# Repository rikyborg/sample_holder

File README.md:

# sample_holder
KTH Nanophys Sample holder

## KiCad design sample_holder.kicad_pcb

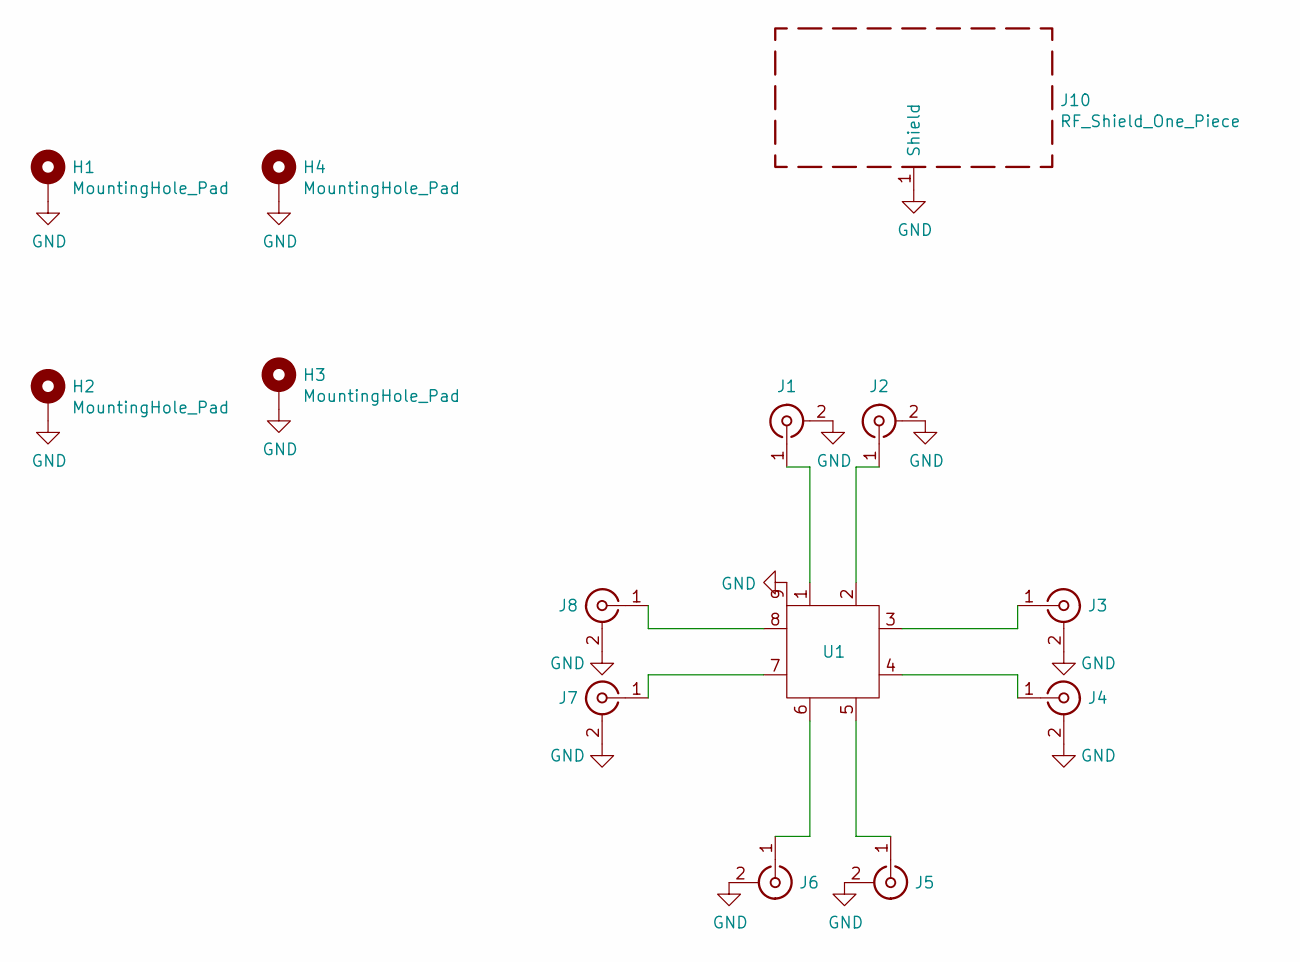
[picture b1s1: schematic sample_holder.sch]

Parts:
H1, H2, H3, H4: MountingHole_Pad; MountingHole_3.5mm_Pad
J1, J2, J3, J4, J5, J6, J7, J8: Conn_Coaxial; 0732513481
J10: RF_Shield_One_Piece; cage
U1: sample

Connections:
GND: H1.1, H2.1, H3.1, H4.1, J1.2 (Ext), J2.2 (Ext), J3.2 (Ext), J4.2 (Ext), J5.2 (Ext), J6.2 (Ext), J7.2 (Ext), J8.2 (Ext), J10.1, U1.9
unnamed: J1.1 (In), U1.1
unnamed: J2.1 (In), U1.2
unnamed: J3.1 (In), U1.3
unnamed: J4.1 (In), U1.4
unnamed: J5.1 (In), U1.5
unnamed: J6.1 (In), U1.6
unnamed: J7.1 (In), U1.7
unnamed: J8.1 (In), U1.8

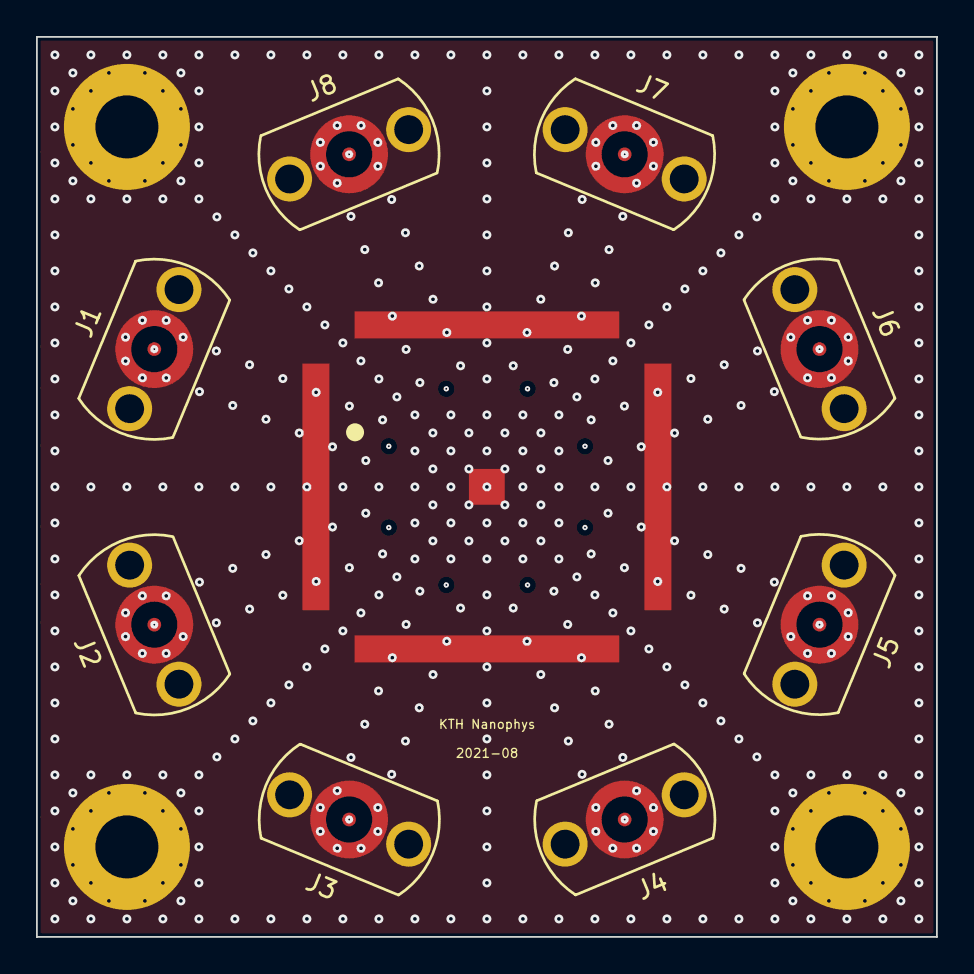
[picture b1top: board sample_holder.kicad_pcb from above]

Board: 4 copper layers, 50.0 x 50.0 mm, 14 parts (0 on the bottom side), 9 nets.

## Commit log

2021-07-10 Create LICENSE
2021-07-16 Update sample_holder
    Update mask
    Update cage mask
2021-07-16 Rename sample_holder to sample_holder.kicad_pcb
2021-10-08 fix up libraries
